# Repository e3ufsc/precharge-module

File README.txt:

View this project on [CADLAB.io](https://cadlab.io/project/30503). 

# template-pcb

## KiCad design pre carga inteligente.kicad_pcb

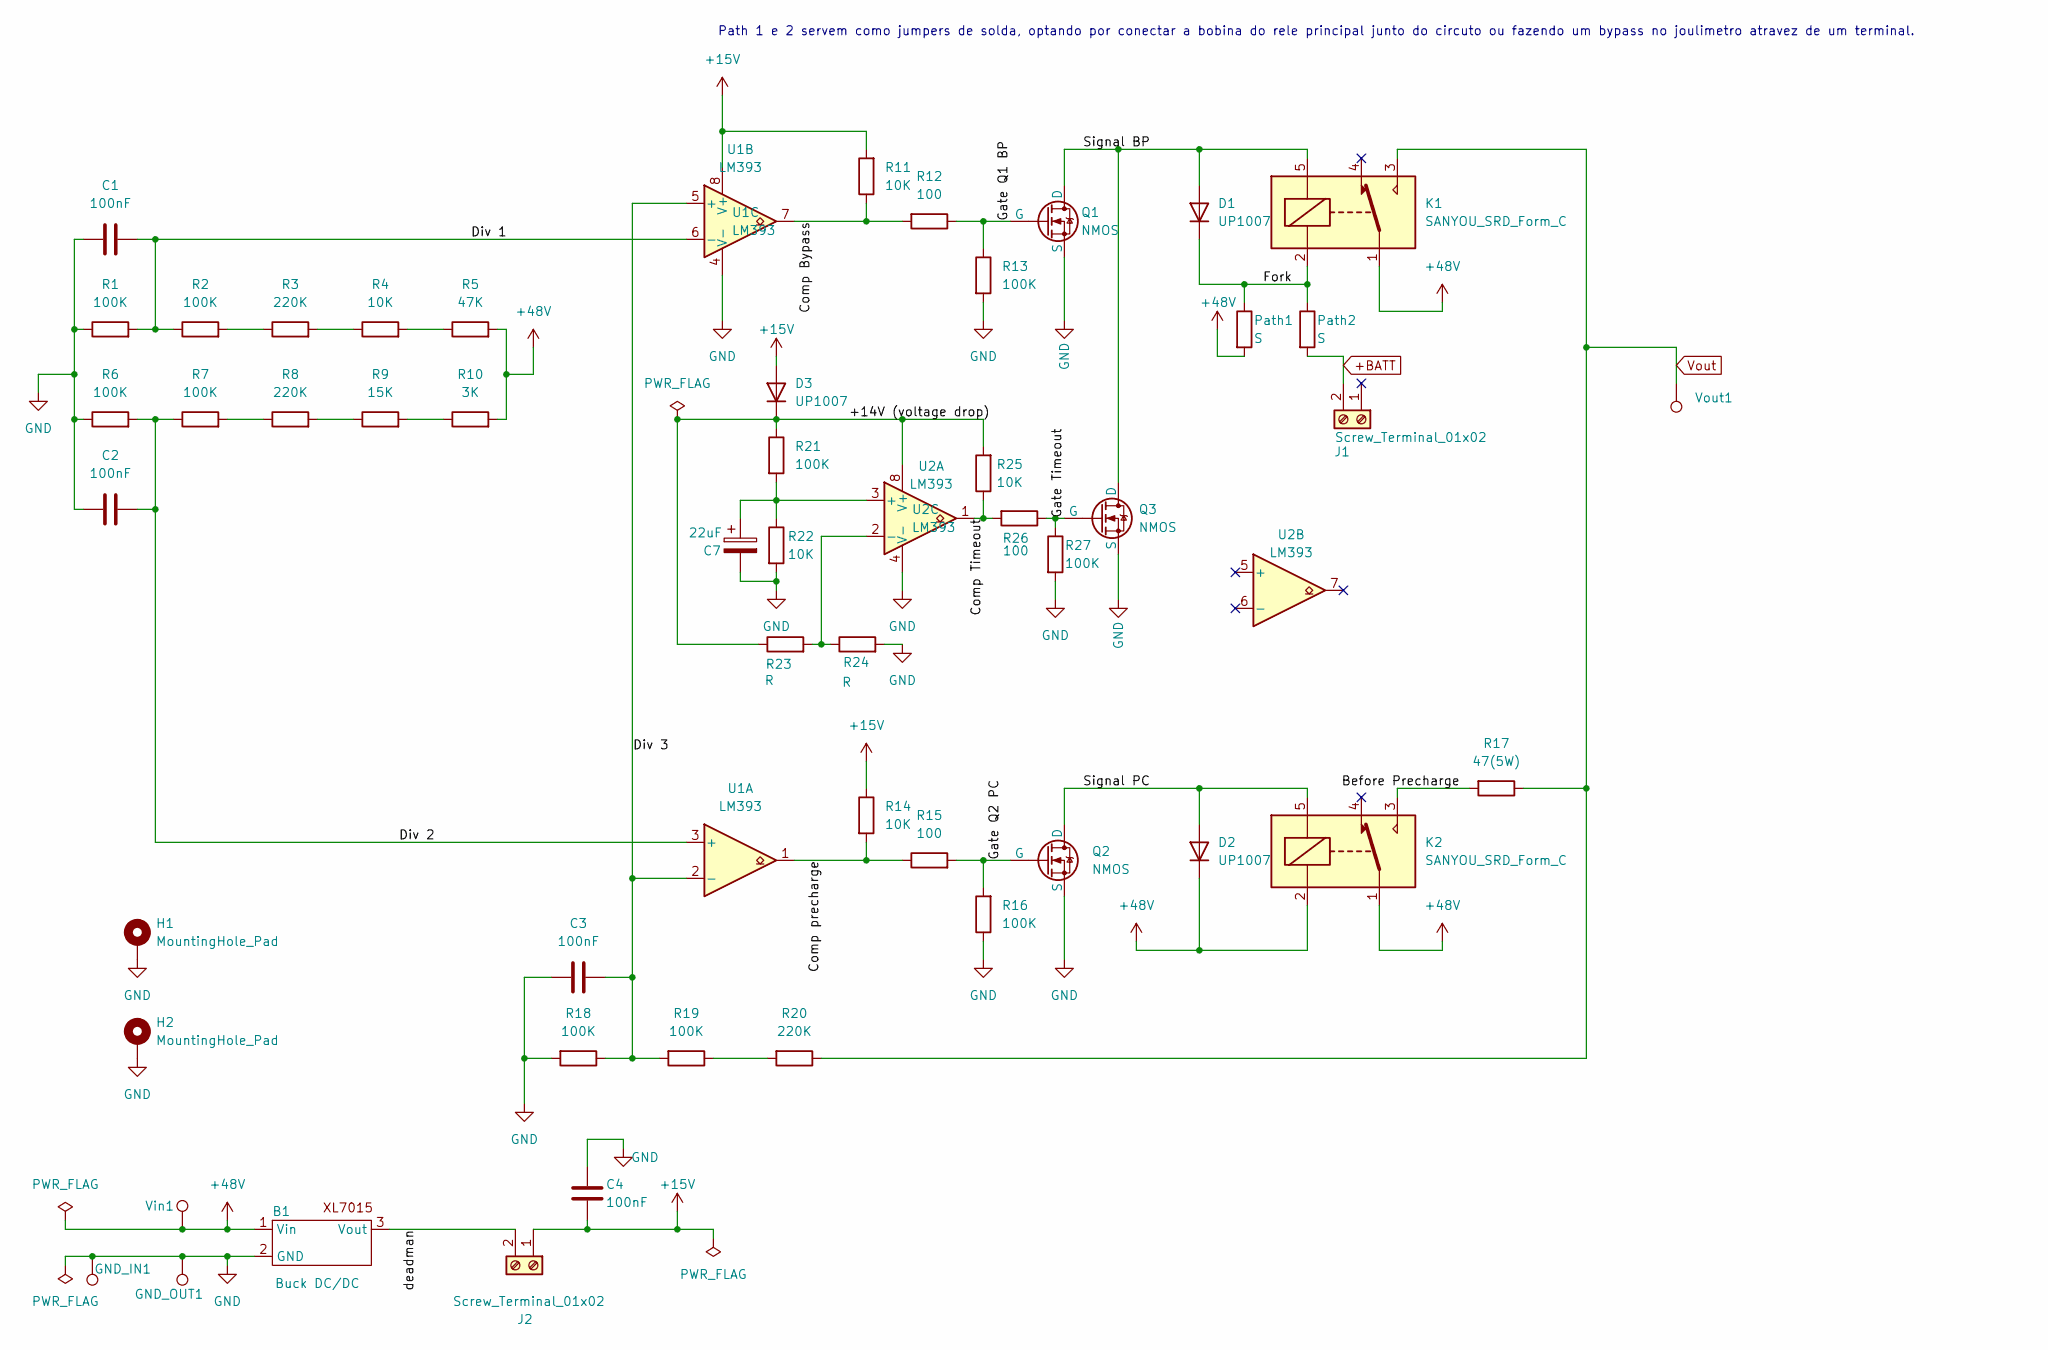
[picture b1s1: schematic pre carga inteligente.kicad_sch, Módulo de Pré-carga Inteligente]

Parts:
B1: Buck DC/DC; XL7015
C1, C2, C3, C4: 100nF; R_Axial_DIN0207_L6.3mm_D2.5mm_P7.62mm_Horizontal
C7: 22uF; CP_Radial_D5.0mm_P2.50mm
D1, D2, D3: UP1007; R_Axial_DIN0207_L6.3mm_D2.5mm_P7.62mm_Horizontal
GND_IN1: GND; 1PAD_8x7mm
GND_OUT1: GND; 1PAD_8x7mm
H1, H2: MountingHole_Pad; MountingHole_3.2mm_M3_ISO7380_Pad
J1, J2: Screw_Terminal_01x02; TerminalBlock_MetzConnect_Type055_RT01502HDWU_1x02_P5.00mm_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
K1, K2: SANYOU_SRD_Form_C; Relay_SPDT_SANYOU_SRD_Series_Form_C
Path1, Path2: S; R_2010_5025Metric_Pad1.40x2.65mm_HandSolder
Q1, Q2, Q3: NMOS; Compact_TO-220-3_Vertical
R1, R2, R6, R7, R13, R16, R18, R19, R21, R27: 100K; R_Axial_DIN0207_L6.3mm_D2.5mm_P7.62mm_Horizontal
R3, R8, R20: 220K; R_Axial_DIN0207_L6.3mm_D2.5mm_P7.62mm_Horizontal
R4, R11, R14, R22, R25: 10K; R_Axial_DIN0207_L6.3mm_D2.5mm_P7.62mm_Horizontal
R5: 47K; R_Axial_DIN0207_L6.3mm_D2.5mm_P7.62mm_Horizontal
R9: 15K; R_Axial_DIN0207_L6.3mm_D2.5mm_P7.62mm_Horizontal
R10: 3K; R_Axial_DIN0207_L6.3mm_D2.5mm_P7.62mm_Horizontal
R12, R15, R26: 100; R_Axial_DIN0207_L6.3mm_D2.5mm_P7.62mm_Horizontal
R17: 47(5W); R_Axial_DIN0617_L17.0mm_D6.0mm_P30.48mm_Horizontal
R23, R24: R; R_Axial_DIN0207_L6.3mm_D2.5mm_P7.62mm_Horizontal
U1, U2: LM393; DIP-8_W7.62mm_Socket
Vin1: Vin; 1PAD_8x7mm
Vout1: Vout; 1PAD_8x7mm

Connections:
+15V: C4.2, D3.2 (A), J2.1, R11.2, R14.1, U1.8 (V+)
+48V: B1.1 (Vin), D2.1 (K), K1.1, K2.1, K2.2, Path1.2, R5.2, R10.2, Vin1.1 (1_1)
+BATT: J1.2 (Pin_2_2), Path2.2
/+14V (voltage drop): D3.1 (K), R21.1, R23.1, R25.2, U2.8 (V+)
/Before Precharge: K2.3, R17.2
/Comp Bypass: R11.1, R12.2, U1.7
/Comp Timeout: R25.1, R26.2, U2.1
/Comp precharge: R14.2, R15.1, U1.1
/Div 1: C1.2, R1.2, R2.1, U1.6 (-)
/Div 2: C2.2, R6.2, R7.1, U1.3 (+)
/Div 3: C3.2, R18.1, R19.2, U1.2 (-), U1.5 (+)
/Fork: D1.1 (K), K1.2, Path1.1, Path2.1
/Gate Q1 BP: Q1.2 (G), R12.1, R13.1
/Gate Q2 PC: Q2.2 (G), R15.2, R16.2
/Gate Timeout: Q3.2 (G), R26.1, R27.1
/Signal BP: D1.2 (A), K1.5, Q1.1 (D), Q3.1 (D)
/Signal PC: D2.2 (A), K2.5, Q2.1 (D)
/deadman: B1.3 (Vout), J2.2
GND: B1.2 (GND), C1.1, C2.1, C3.1, C4.1, C7.2, GND_IN1.1 (1_1), GND_OUT1.1 (1_1), H1.1 (1_1), H2.1 (1_1), Q1.3 (S), Q2.3 (S), Q3.3 (S), R1.1, R6.1, R13.2, R16.1, R18.2, R22.2, R24.2, R27.2, U1.4 (V-), U2.4 (V-)
unnamed: R2.2, R3.1
unnamed: R3.2, R4.1
unnamed: R4.2, R5.1
unnamed: R7.2, R8.1
unnamed: R8.2, R9.1
unnamed: R9.2, R10.1
unnamed: R19.1, R20.2
unnamed: C7.1, R21.2, R22.1, U2.3 (+)
unnamed: R23.2, R24.1, U2.2 (-)
Vout: K1.3, R17.1, R20.1, Vout1.1 (1_1)

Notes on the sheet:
Path 1 e 2 servem como jumpers de solda, optando por conectar a bobina do rele principal junto do circuto ou fazendo um bypass no joulimetro atravez de um terminal.

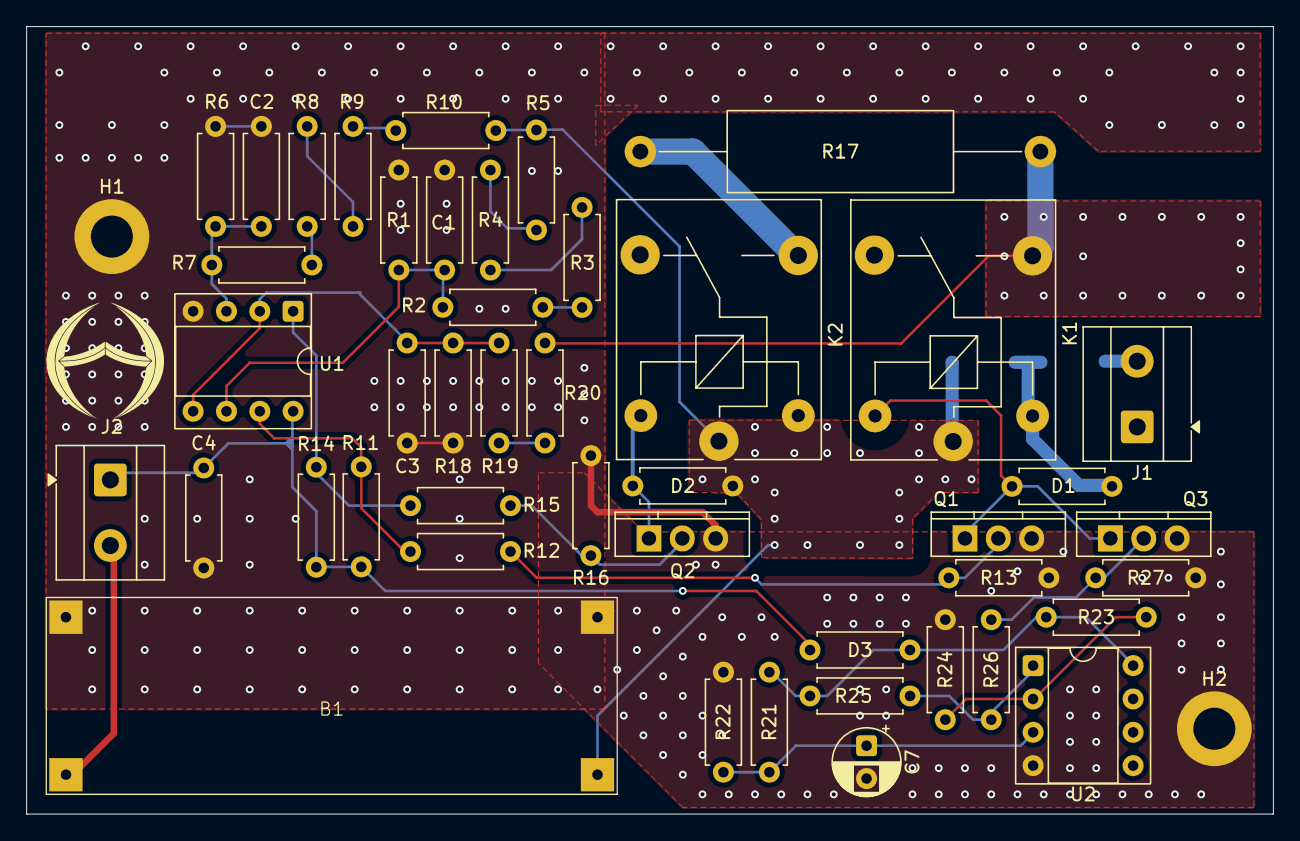
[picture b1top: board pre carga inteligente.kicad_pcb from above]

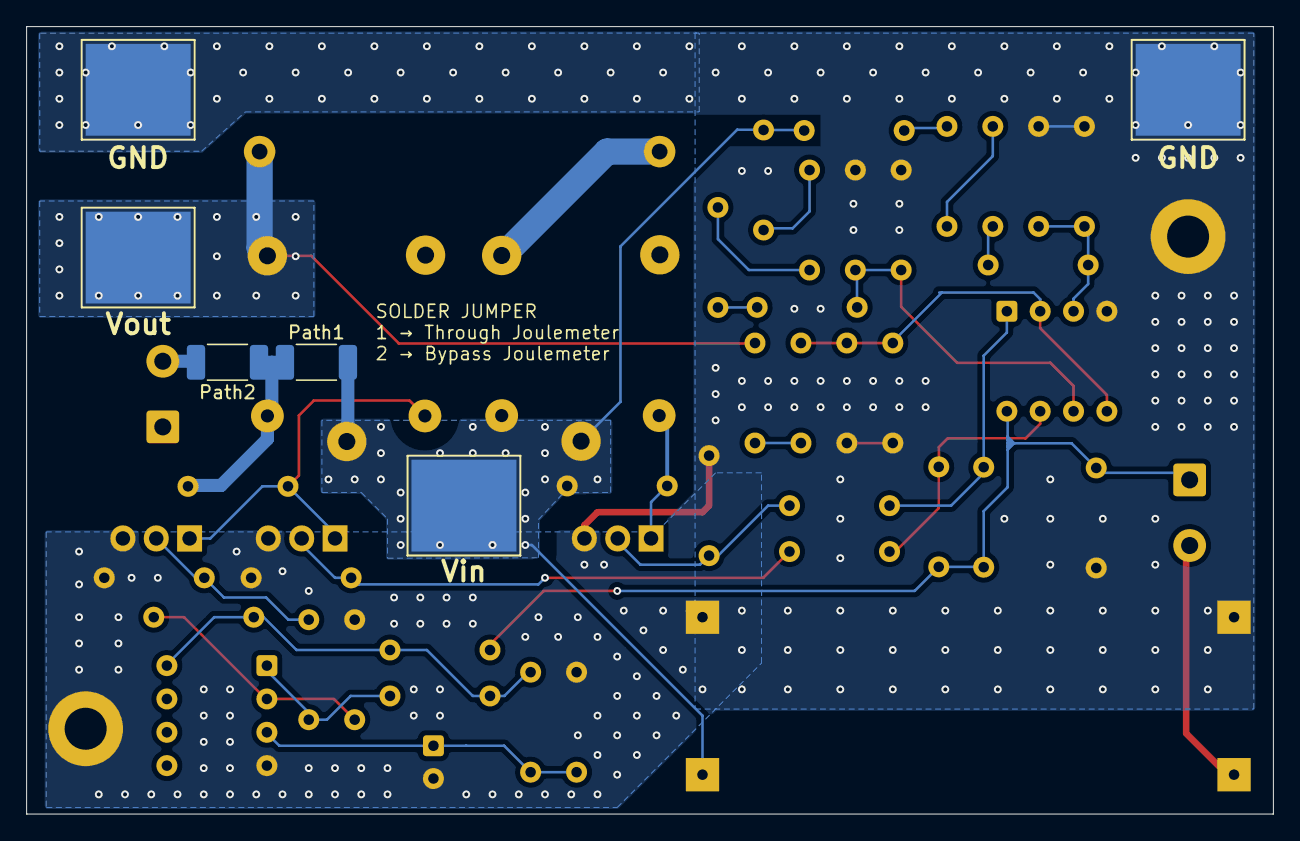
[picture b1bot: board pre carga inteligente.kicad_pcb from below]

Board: 2 copper layers, 95.0 x 60.0 mm, 53 parts (6 on the bottom side), 29 nets.
